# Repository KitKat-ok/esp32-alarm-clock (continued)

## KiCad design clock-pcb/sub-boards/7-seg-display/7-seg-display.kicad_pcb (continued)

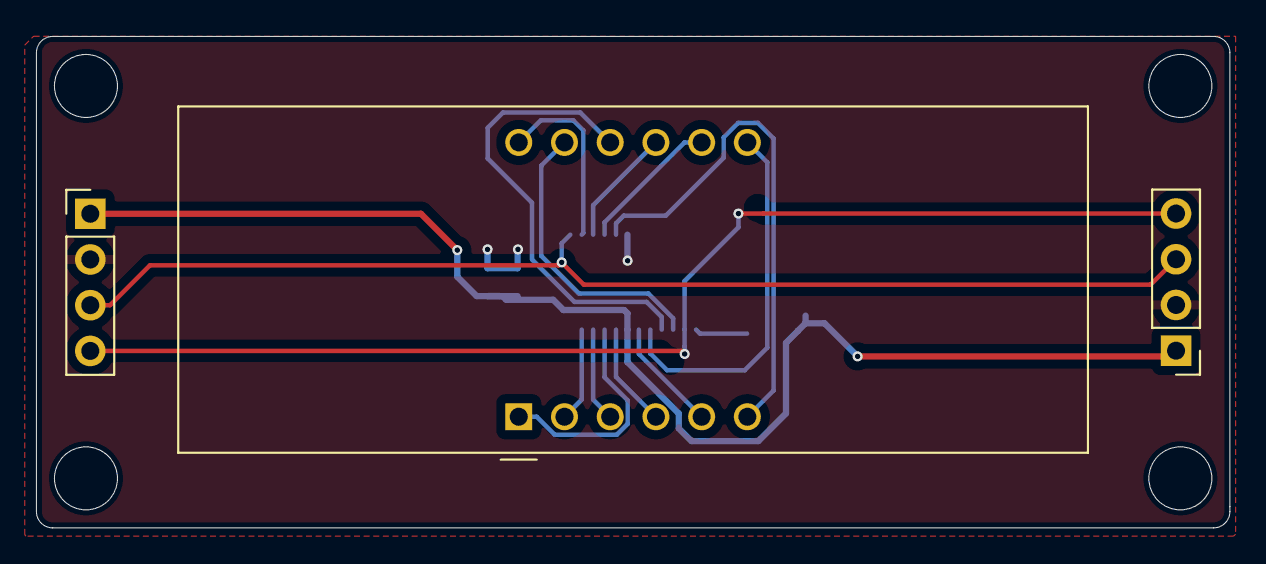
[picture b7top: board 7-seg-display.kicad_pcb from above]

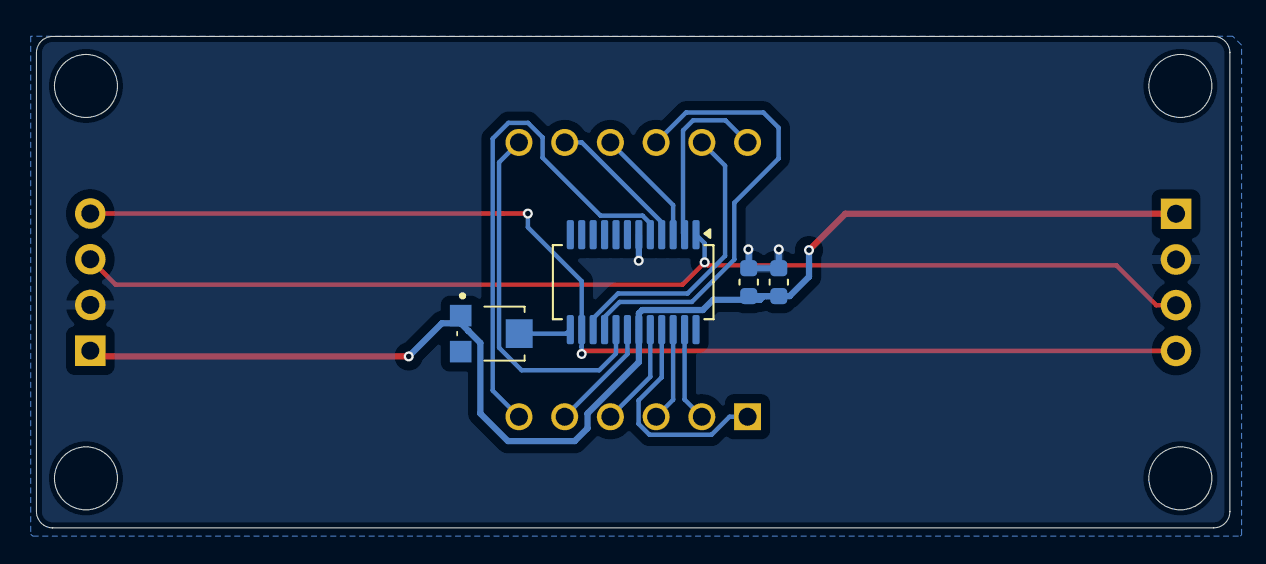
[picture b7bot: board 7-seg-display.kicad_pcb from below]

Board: 2 copper layers, 66.3 x 27.3 mm, 7 parts (4 on the bottom side), 17 nets.

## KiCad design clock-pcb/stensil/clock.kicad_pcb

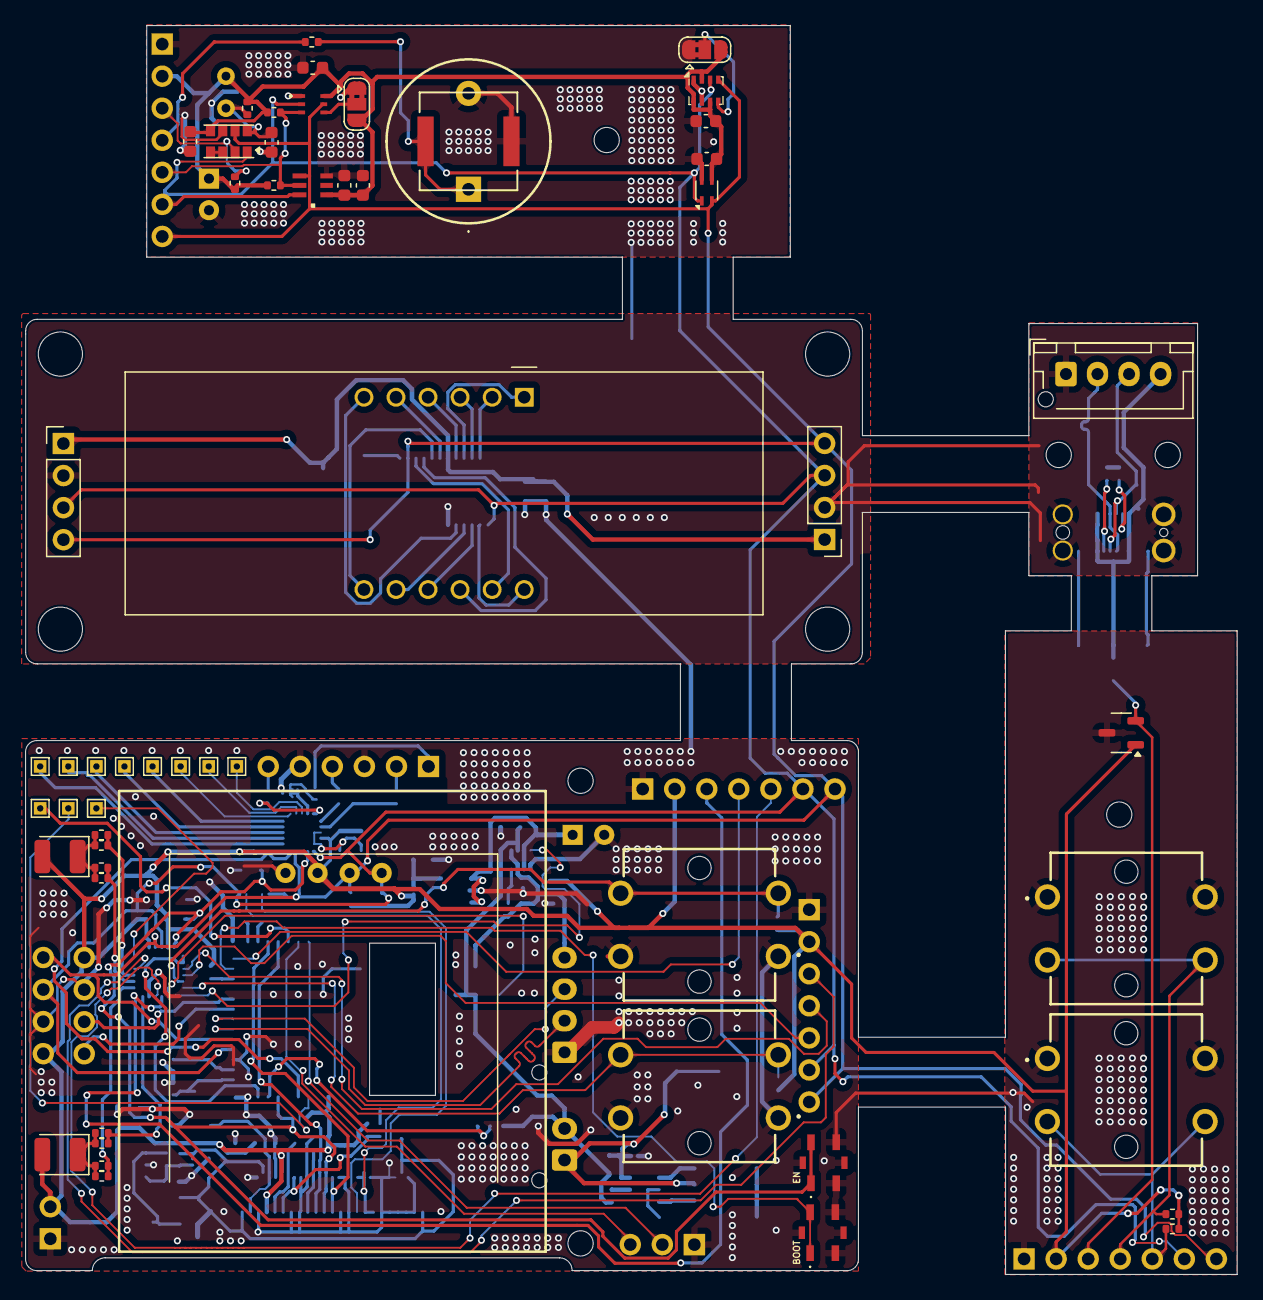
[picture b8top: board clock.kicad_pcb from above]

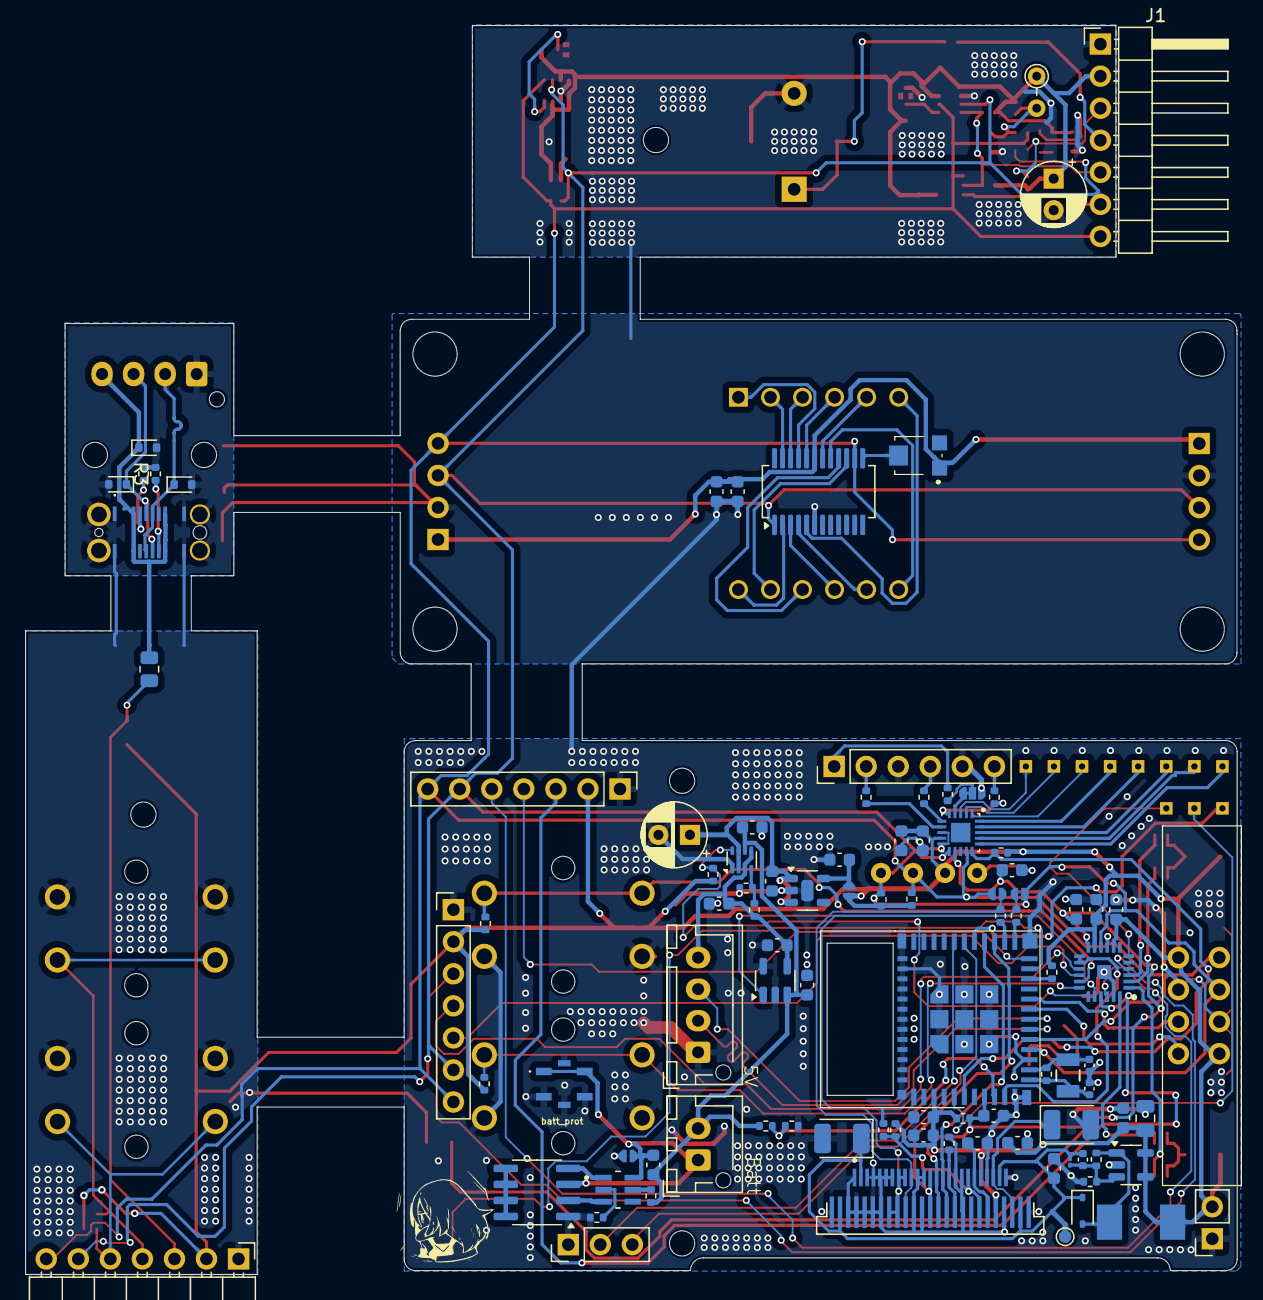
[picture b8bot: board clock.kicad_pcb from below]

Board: 2 copper layers, 96.0 x 99.0 mm, 154 parts (95 on the bottom side), 98 nets.

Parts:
AO9926C1: SOIC-8_3.9x4.9mm_P1.27mm
C1, C1#2, C2, C2#2, C3, C4#2, C6, C23, C23#2: 0.1uF; C_0603_1608Metric
C3#2, C17, C24, C24#2: 10uF; C_0603_1608Metric
C4: 4.7uF; C_0603_1608Metric
C5, C6#2, C7, C8, C9, C10, C11, C12, C13, C13#2, C14, C15, C21, C25, C28: 1uF; C_0603_1608Metric
C5#2, C7#2: 100uF; CP_Radial_D5.0mm_P2.50mm
C16: 4.7uF; C_0805_2012Metric
C18: 6.4pF; C_0402_1005Metric
C19, C20: 19pF; C_0402_1005Metric
C22: 6.4pF; C_01005_0402Metric
C26, C27: 4.7uF; CP_EIA-3528-12_Kemet-T
D1, D2: LED; LED_1210_3225Metric
D1#2, D2#2, D3#2: ESD5Zxx; D_SOD-523
D3: NSVR0340HT1G; D_SOD-323
IC1: VEML6030-GS15; VEML6030GS15
IC2: MCP23018-E_MJ; QFN50P400X400X90-25N-D
J1, J2: Conn_01x04_Socket; PinHeader_1x04_P2.54mm_Vertical
J1#2, J1#3: Conn_01x07_Socket; PinHeader_1x07_P2.54mm_Horizontal
J1#4: Conn_01x03_Pin; PinHeader_1x03_P2.54mm_Vertical
J1#5: USB4145-03-0070-C; USB4145030070C
J2#2: oled 2; SSD1306_0.96_Oled
J3: Led display; tm1637_module
J4: Led display 2; PinHeader_1x04_P2.54mm_Vertical
J5, J6: Conn_01x07_Socket; PinHeader_1x07_P2.54mm_Vertical
J7: SFV25R-2STE1HLF; OLED_1.5IN_128X128MONO
J8, J9: Conn_01x04_Socket; JST_XH_B4B-XH-AM_1x04_P2.50mm_Vertical
J8#2: SFV25R-2STE1HLF; AMPHENOL_SFV25R-2STE1HLF
J11: Conn_01x06_Socket; PinHeader_1x06_P2.54mm_Vertical
J15: Conn_01x02_Socket; PinSocket_1x02_P2.54mm_Vertical
JP1, JP2: SolderJumper_3_Bridged12; SolderJumper-3_P1.3mm_Bridged2Bar12_RoundedPad1.0x1.5mm
JP1#2, JP5, JP6, JP7: Jumper; jumper_solder_small
JP2#2: SolderJumper_3_Bridged12; jumper_solder_small_3_bridged
L1: CPT-14146-80T; CPT1414680T
L1#2: 10uH 1A; HPI0530-100
LS1: Speaker_Crystal; AST0760_MAL
R0, R1#4, R3#2: 5.1k; R_0402_1005Metric
R1, R1#2, R2, R3, R6, R8, R9, R10, R11, R11#2, R15, R16, R28, R30, R31: 10K; R_0402_1005Metric
R1#3, R12, R14: 100k; R_0402_1005Metric
R2#2, R26: 300k; R_0402_1005Metric
R3#3: 800k; R_0402_1005Metric
R4, R4#2: 330R; R_0402_1005Metric
R5: 22R; R_0402_1005Metric
R5#2: 2.7K; R_0402_1005Metric
R6#2: 22R; R_Axial_DIN0204_L3.6mm_D1.6mm_P2.54mm_Vertical
R7: 47K; R_0402_1005Metric
R13: 250k; R_0402_1005Metric
R17, R18, R19, R20, R22, R23, R24, R25: 330; R_0402_1005Metric
R21: 10M; R_0402_1005Metric
R27: 3.16M; R_0402_1005Metric
R29: 1.2M; R_0402_1005Metric
R32, R33: N/A; R_0402_1005Metric
S1, S2, S3, S4: B3F-5050; B3F-4055
S1#2, S2#2, S5: TS21-34-035-BK-160-SMT-TR; TS2134035BK160SMTTR
TP1, TP3, TP4, TP5, TP6, TP7, TP8, TP9, TP10, TP12, TP13: TestPoint; TestPoint_THTPad_1.0x1.0mm_Drill0.5mm
TP2: TestPoint; TestPoint_Pad_D1.0mm
U1: BMP280; Bosch_LGA-8_2x2.5mm_P0.65mm_ClockwisePinNumbering
U1#2: CC56-12EWA; CA56-12EWA
U1#3: TMAG5231C1GQDBZR; SOT-23-3
U1#4: ESP32-C6-MINI-1-N4; XCVR_ESP32-C6-MINI-1-N4
U2: LTR-F216A
U2#2: AS1115-BSST; QSOP-24_3.9x8.7mm_P0.635mm
U2#3: SOT95P280X140-6N
U3: APDS-9960; Avago_APDS-9960
U3#2: JST_XH_B2B-XH-AM_1x02_P2.50mm_Vertical
U4: SHT4x; Sensirion_DFN-4_1.5x1.5mm_P0.8mm_SHT4x_NoCentralPad
U4#2: TPS2116DRL; SOT-583-8
U5: MCP73811T-420I-OT; SOT-23-5
U6: TPS61040DBV; SOT-23-5
U7: TLV75533PDBV; TLV75733PDYDR
U8: AT42QT2120-MMHR; QFN45P300X300X85-21N
VR1: TC33X-2-303E; TC33X2304E
Y2: 32.768KHz; XTAL_9HT10_TXC

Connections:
14V_OLED: C17.1, C18.1, C22.1, C27.1, D3.1 (K), J7.2, J7.24, J8#2.2, J8#2.24, TP2.1
+3.3V: C23.1, C24#2.1, J1.1, J2.1, U2#2.19 (VDD), VR1.1 (CCW)
+3V3: C1.2, C1#2.2, C2.2, C2#2.1, C3.1, C3#2.1, C4.1, C6.2, C7#2.1, C13.1, C15.2, C16.1, C21.2, C23#2.1, C24.1, C28.2, D1.2 (A), D2.2 (A), IC1.6 (VDD), IC2.8 (VDD), IC2.11 (ADDR), J1#2.2, J1#3.2, J2#2.2, J3.4, J4.4, J5.2, J6.2, J7.5, J8#2.21, J15.2, JP1.3 (B), JP2.3 (B), JP7.2 (B), L1#2.2, R0.1, R1.2, R1#2.1, R1#3.1, R2.1, R3.1, R5.1, R6.2, R6#2.1, R7.1, R11.2, R11#2.1, R12.1, R15.2, R28.2, R31.1, U1.2 (CSB), U1.6 (VDDIO), U1.8 (VDD), U1#3.1 (VCC), U1#4.3 (3V3), U2.1 (VDD), U3.5 (LED_A), U4.3 (VDD), U6.4 (EN), U6.5 (VIN), U8.9 (VDD)
+BATT: C4#2.2, C7.1, C11.1, R2#2.1, R4#2.2, U3#2.2, U4#2.6 (VIN2), U5.3 (V_{BAT})
-BATT: AO9926C1.3 (S1), C4#2.1, JP1#2.1 (A), S5.1 (COM_1), S5.2 (COM_2), U2#3.6 (VSS), U3#2.1
ADC: R2#2.2, R3#3.1, U1#4.9 (IO4)
BUTON_CONF: IC2.16 (GPA1), J1#3.5, J6.5, R11.1, S1.3 (NO_1), S1.4 (NO_2)
BUTTON_DOWN: IC2.18 (GPA3), R28.1, S4.3 (NO_1), S4.4 (NO_2)
BUTTON_EXIT: IC2.15 (GPA0), J1#3.4, J6.4, R1.1, S2.3 (NO_1), S2.4 (NO_2)
BUTTON_UP: IC2.17 (GPA2), R15.1, S3.3 (NO_1), S3.4 (NO_2)
BUZZER: J1#2.4, J5.4, R4.2, U1#4.24 (IO18)
BUZZER_IN: L1.1, LS1.1, R4.1
CHARGE_EN: IC2.20 (GPA5), U5.1 (CE)
CLK: J4.1, U1#4.19 (IO14)
CLOCK_N: C19.1, R21.1, U1#4.13 (IO1), Y2.1
CLOCK_P: C20.1, R21.2, U1#4.12 (IO0), Y2.2
CS: J7.11, J8#2.15, U1#4.28 (IO22)
DC: J7.13, J8#2.13, U1#4.27 (IO21)
DIGIT-1: U1#2.12 (CC1), U2#2.2 (DIG0)
DIGIT-2: U1#2.9 (CC2), U2#2.3 (DIG1)
DIGIT-3: U1#2.8 (CC3), U2#2.4 (DIG2)
DIGIT-4: U1#2.6 (CC4), U2#2.5 (DIG3)
DIO: J4.2, U1#4.20 (IO15)
DN: D2#2.1 (K), J1#5.A7 (DN1), J1#5.B7 (DN2), J8.2, J9.2, U1#4.17 (IO12)
DP: D3#2.1 (K), J1#5.A6 (DP1), J1#5.B6 (DP2), J8.3, J9.3, U1#4.18 (IO13)
EN: C12.2, C13#2.1, C14.2, IC2.12 (~RESET), J7.12, J8#2.14, R11#2.2, S2#2.1 (COM_1), S2#2.2 (COM_2), U1#4.8 (EN), U8.12 (~RESET)
GND: AO9926C1.1 (S2), C1.1, C1#2.1, C2.1, C2#2.2, C3.2, C3#2.2, C4.2, C5.2, C5#2.2, C6.1, C6#2.1, C7.2, C7#2.2, C8.2, C9.2, C10.2, C11.2, C12.1, C13.2, C13#2.2, C14.1, C15.1, C16.2, C17.2, C19.2, C20.2, C21.1, C23.2, C23#2.2, C24.2, C24#2.2, C25.1, C26.2, C27.2, C28.1, D1#2.2 (A), D2#2.2 (A), D3#2.2 (A), IC1.1 (GND), IC2.23 (VSS), IC2.25 (EP), J1.2, J1#2.1, J1#3.1, J1#4.1, J1#5.A1 (GND_1), J1#5.A12 (GND_2), J1#5.B1 (GND_3), J1#5.B12 (GND_4), J1#5.MH1, J1#5.MH2, J1#5.MH3, J1#5.MH4, J2.2, J2#2.1, J3.3, J4.3, J5.1, J6.1, J7.1, J7.4, J7.8, J7.9, J7.14, J7.15, J7.19, J7.20, J7.21, J7.22, J7.23, J7.25, J8.1, J8#2.1, J8#2.3, J8#2.4, J8#2.5, J8#2.6, J8#2.7, J8#2.11, J8#2.12, J8#2.17, J8#2.18, J8#2.22, J8#2.25, J9.1, J11.3, J11.5, J15.1, JP1.1 (A), JP1#2.2 (B), JP2.1 (A), JP2#2.3 (B), L1.2, LS1.2, R1#4.2, R3#2.2, R3#3.2, R5#2.2, R14.1, R26.2, R29.2, R30.1, S1.1 (COM_1), S1.2 (COM_2), S1#2.3 (NO_1), S1#2.4 (NO_2), S1#2.MP1, S1#2.MP2, S2.1 (COM_1), S2.2 (COM_2), S2#2.3 (NO_1), S2#2.4 (NO_2), S2#2.MP1, S2#2.MP2, S3.1 (COM_1), S3.2 (COM_2), S4.1 (COM_1), S4.2 (COM_2), S5.3 (NO_1), S5.4 (NO_2), S5.MP1, S5.MP2, U1.1 (GND), U1.7 (GND), U1#3.3 (GND), U1#4.1 (GND1), U1#4.2 (GND1__1), U1#4.11 (GND1__2), U1#4.14 (GND1__3), U1#4.36 (GND1__4), U1#4.37 (GND1__5), U1#4.38 (GND1__6), U1#4.39 (GND1__7), U1#4.40 (GND1__8), U1#4.41 (GND1__9), U1#4.42 (GND1__10), U1#4.43 (GND1__11), U1#4.44 (GND1__12), U1#4.45 (GND1__13), U1#4.46 (GND1__14), U1#4.47 (GND2), U1#4.48 (GND2__1), U1#4.49_1 (GND2__2), U1#4.49_2 (GND2__3), U1#4.49_3 (GND2__4), U1#4.49_4 (GND2__5), U1#4.49_5 (GND2__6), U1#4.49_6 (GND2__7), U1#4.49_7 (GND2__8), U1#4.49_8 (GND2__9), U1#4.49_9 (GND2__10), U1#4.50 (GND2__11), U1#4.51 (GND2__12), U1#4.52 (GND2__13), U1#4.53 (GND2__14), U2.3 (GND), U2#2.6 (GND), U3.6 (GND), U4.4 (VSS), U4#2.1 (GND), U5.2 (V_{SS}), U5.5 (PROG), U6.2 (GND), U7.2 (GND), U8.8 (VSS), U8.10 (MODE)
GPIO9: S1#2.1 (COM_1), S1#2.2 (COM_2), U1#4.23 (IO9)
GUARD: JP2#2.1 (A), JP2#2.2 (C), R9.2, U8.4 (KEY3/GPO1)
HALL_SENS: IC2.4 (GPB4), J1#3.3, J6.3, U1#3.2 (OUT)
INT_A: IC2.13 (INTB), IC2.14 (INTA), U1#4.10 (IO5)
LDO_IN: C5#2.1, C9.1, U4#2.2 (VOUT), U4#2.7 (VOUT), U7.1 (IN), U7.3 (EN)
LED1_P1: IC2.24 (GPB0), R17.1, R19.1
LED1_P2: IC2.1 (GPB1), R18.1, R20.1
LED2_P1: IC2.2 (GPB2), R22.1, R23.1
LED2_P2: IC2.3 (GPB3), R24.1, R25.1
MOSI: J7.17, J7.18, J8#2.8, J8#2.9, JP5.2 (B), R33.1
unnamed: AO9926C1.5 (D1), AO9926C1.6 (D1), AO9926C1.7 (D2), AO9926C1.8 (D2)
unnamed: AO9926C1.4 (G1), U2#3.1 (DO)
unnamed: AO9926C1.2 (G2), U2#3.3 (CO)
unnamed: C25.2, J7.6, J8#2.20
unnamed: C26.1, J7.3, J8#2.23
unnamed: D1.1 (K), R17.2, R18.2, R19.2, R20.2
unnamed: D2.1 (K), R22.2, R23.2, R24.2, R25.2
unnamed: D3.2 (A), L1#2.1, R27.1, U6.1 (SW)
unnamed: IC1.4 (ADDR), JP1.2 (C)
unnamed: IC2.6 (GPB6), TP10.1
unnamed: J1#5.A5 (CC1), R1#4.1
unnamed: J1#5.B5 (CC2), R3#2.1
unnamed: J7.7, J8#2.19, R30.2, R31.2
unnamed: J7.10, J8#2.16, R29.1
unnamed: J11.1, R9.1
unnamed: J11.2, R16.1
unnamed: J11.4, R10.1
unnamed: J11.6, R8.1
unnamed: JP2.2 (C), U1.5 (SDO)
unnamed: C8.1, JP7.1 (A), U7.5 (OUT)
unnamed: U1#2.3 (DPX), U2#2.22 (SEGDP)
unnamed: TP9.1, U1#4.5 (IO2)
unnamed: R0.2, U1#4.22 (IO8)
unnamed: R33.2, U1#4.25 (IO19)
unnamed: R32.2, U1#4.26 (IO20)
unnamed: TP1.1, U1#4.29 (IO23)
unnamed: U1#2.11 (a), U2#2.15 (SEGA)
unnamed: U1#2.7 (b), U2#2.17 (SEGB)
unnamed: U1#2.4 (c), U2#2.20 (SEGC)
unnamed: U1#2.2 (d), U2#2.23 (SEGD)
unnamed: U1#2.1 (e), U2#2.21 (SEGE)
unnamed: U1#2.10 (f), U2#2.16 (SEGF)
unnamed: U1#2.5 (g), U2#2.18 (SEGG)
unnamed: U2#2.13 (ISET), VR1.2 (WIPER)
unnamed: R4#2.1, U2#3.5 (VDD)
unnamed: R5#2.1, U2#3.2 (VM)
unnamed: U3.3 (LDR), U3.4 (LED_K)
unnamed: C5.1, R5.2, R6#2.2, U3.8 (VDD)
unnamed: R13.1, R14.2, U4#2.4 (PR1)
unnamed: C18.2, C22.2, R26.1, R27.2, U6.3 (FB)
unnamed: TP13.1, U8.3 (KEY4/GPO2)
unnamed: TP12.1, U8.2 (KEY5/GPO3)
unnamed: TP8.1, U8.1 (KEY6/GPO4)
unnamed: TP7.1, U8.20 (KEY7/GPO5)
unnamed: TP6.1, U8.19 (KEY8/GPO6)
unnamed: TP5.1, U8.18 (KEY9/GPO7)
unnamed: TP4.1, U8.17 (KEY10/GPO8)
unnamed: TP3.1, U8.16 (KEY11/GPO9)
POWER_STATUS: IC2.19 (GPA4), R6.1, U4#2.8 (ST)
RX: J1#4.3, U1#4.30 (RXD0)
SCL: IC1.5 (SCL), IC2.9 (SCL), J1.4, J1#2.7, J1#3.7, J2.4, J2#2.3, J3.1, J5.7, J6.7, JP6.1 (A), R1#3.2, U1.4 (SCK), U1#4.16 (IO7), U2.4 (SCL), U2#2.14 (SCL), U3.7 (SCL), U4.2 (SCL), U8.14 (SCL)
SCLK: J7.16, J8#2.10, JP6.2 (B), R32.1
SDA: IC1.2 (SDA), IC2.10 (SDA), J1.3, J1#2.6, J1#3.6, J2.3, J2#2.4, J3.2, J5.6, J6.6, JP5.1 (A), R12.2, U1.3 (SDI), U1#4.15 (IO6), U2.6 (SDA), U2#2.1 (SDA), U3.1 (SDA), U4.1 (SDA), U8.11 (SDA)
SLID_0: R16.2, U8.7 (KEY0)
SLID_1: R10.2, U8.6 (KEY1)
SLID_2: R8.2, U8.5 (KEY2/GPO0)
SUB_TOP_1: IC1.3 (INT), IC2.22 (GPA7), J1#2.5, J5.5, R1#2.2, R2.2, U2.5 (INT)
SUB_TOP_3: IC2.21 (GPA6), J1#2.3, J5.3, R3.2, U3.2 (INT)
TOUCH_INT: R7.2, U1#4.6 (IO3), U8.15 (~CHANGE)
TX: J1#4.2, U1#4.31 (TXD0)
VBUS: C6#2.2, C10.1, D1#2.1 (K), J1#5.A4 (VBUS_1), J1#5.A9 (VBUS_2), J1#5.B4 (VBUS_3), J1#5.B9 (VBUS_4), J8.4, J9.4, R13.2, U4#2.3 (VIN1), U4#2.5 (MODE), U5.4 (V_{DD})

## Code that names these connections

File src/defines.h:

#ifndef DEFINES_H
#define DEFINES_H

#include "fonts/fonts.h"
#include "weather/weathericons.h"

#include <Arduino.h>
#include <Adafruit_GFX.h>
#include <Adafruit_SSD1306.h>
#include <TM1637Display.h>
#include <BH1750.h>
#include <WiFi.h>
#include <WiFiMulti.h>
#include <TimeLib.h>
#include <NTPClient.h>
#include <Preferences.h>
#include <OneWire.h>
#include <DallasTemperature.h>
#include <oledManager.h>

extern bool OTAEnabled;

// Led Display
#define CLK  19 // The ESP32 pin GPIO22 connected to CLK
#define DIO  18 // The ESP32 pin GPIO23 connected to DIO

// NTP
#define TIME_OFFSET_S 3600            // Time offset in seconds, use this as timezones

// Weather
#define DAILY_WEATHER_INTERVAL 5 * 60 * 60 * 1000
#define CURRENT_WEATHER_INTERVAL 30 * 60 * 1000  // 30 minutes

// Light Sensor
#define OLED_DISABLE_THRESHOLD 45
#define LED_DIM_THRESHOLD 30
#define LED_DISABLE_THRESHOLD 1

#define MAX_INCREASE_OF_LIGHT_LEVEL 1000

// Inputs
#define BUTTON_UP_PIN      GPIO_NUM_12
#define BUTTON_DOWN_PIN    GPIO_NUM_13
#define BUTTON_CONFIRM_PIN GPIO_NUM_14
#define BUTTON_EXIT_PIN    GPIO_NUM_15

#define MAX_MENU_ITEMS 15
#define MAX_ALARMS 15


#define TOUCH_BUTTON_PIN 4
#define TOUCH_BUTTON_THRESHOLD 8
#define TOUCH_BUTTON_THRESHOLD_WHEN_ALREADY_TOUCHED 8
#define TOUCH_BUTTON_THRESHOLD_ON_BATTERY 9

#define NUM_TOUCH_SAMPLES 10

// Menus
#define TOTAL_NAV_BUTTONS 4
#define MAX_DEPTH 20

#define MAIN_PAGE_DURATION 60000
#define SCREENSAVER_DURATION 30000

#define N_FLYERS 5  // Numver of flyers on screensaver

#define fontX 6
//5
#define fontY 12

// Alarm
#define SUNDAY    0
#define MONDAY    1
#define TUESDAY   2
#define WEDNESDAY 3
#define THURSDAY  4
#define FRIDAY    5
#define SATURDAY  6

// Buzzer
#define BUZZER_PIN 27
//#define START_SOUND false // uncomment to enable start sound

// Battery
#define MIN_VOLTAGE 3.40  // Minimum voltage of LiPo battery
#define MAX_VOLTAGE 4.20  // Maximum voltage of LiPo battery
#define NUM_SAMPLES 15   // How many samples to read to smooth the voltage out

#define VOLTAGE_DIVIDER_PIN 34 

#define FULLY_CHARGED_PIN 32
#define CHARGING_PIN 33

#define TIMER_WAKUP_TIME 15000 // In miliseconds
#define GPIO_WAKUP_TIME 30000 // In miliseconds
#define SLEEPING_TIME 60 * 1000000 

#define CHARGING_THRESHOLD 1000
#define STANDBY_THRESHOLD 1000

// Temperature
#define TEMP_SENS_PIN 5
#define TEMP_CHART_READINGS 55 // Number of readings to keep

#define TEMP_OFFSET 2.77


#include "hardware/pitches.h"

#include "confidential.h"

#include "hardware/hardware.h"
#include "functions.h"
#include "WiFi/WiFi.h"
#include "NTP/NTP.h"
#include "weather/weather.h"
#include "LedDisplay/LedDisplay.h"
#include "lightSensor/lightSensor.h"
#include "oledDisplay/interface.h"
#include "oledDisplay/mainPage.h"
#include "oledDisplay/charts.h"
#include "oledDisplay/menus.h"
#include "Flash/Flash.h"
#include "alarms/alarms.h"
#include "battery/battery.h"
#include "tempSensor/tempSensor.h"


#endif

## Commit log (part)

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2023-12-31 platformio
2024-01-01 touch button
2024-01-04 battery
2024-01-05 battery not working
2024-01-09 sleep management
2024-01-10 temperature
2024-01-11 Temp chart
2024-01-12 temp working yep maybe
2024-01-13 temp sync
2024-01-13 fixed the chart
2024-01-16 weather menu menu fixes and light chart
2024-01-16 to do
2024-01-21 different temp sensor
2024-02-04 test?
2024-03-20 probably fixed a few bugs
2024-04-04 fixed many issues
2024-04-13 fixes of crashes, added debug menus
2024-04-19 added ringing bool and fixed the brightness modulation
2024-04-21 forgot to save the soundOn variable....
2024-04-23 completly redesigned the main page
2024-04-26 cleaned up files
2024-04-26 added comment
2024-05-01 probably fixed some issues with light readings
2024-05-03 fixed a bit of weather menus
2024-05-07 fixed name of alarm structure and added confidential file
2024-05-07 chaged gitignore
2024-05-07 test
2024-05-07 test2
2024-05-07 added confidential
2024-05-07 cleaned up
2024-05-08 cleaned up code again...
2024-05-08 cleaned up again
2024-05-09 checking for night is now dependant on alarms
2024-05-10 cleaned up some stuff
2024-05-11 changed ringing alarm structure
2024-05-11 didnt compile lol
2024-05-11 fixed wrong if
2024-05-23 fixed file name and added OTA in menus
2024-05-25 time wasnt updating on alarm
2024-06-06 fixed a bit of stuff
2024-06-16 added screensaver to prevent burnin
2024-06-17 added second main to sleep menu and dimming is better
2024-06-21 fixed bugs
2024-06-22 fixed crashes and started using internal rtc to keep time even if a crash occurs
2024-06-22 added voltage to debug changed start sound
2024-06-23 fixed alighnment on main menu
2024-06-27 changed threshold
2024-07-01 changed some stuff
2024-07-25 cleaned up code, switched to openmeteo, fixed bugs
2024-07-25 changed confidential file
2024-07-25 updated plaformio.ini
2024-07-25 added a delay
2024-07-25 moved link to confidential
2024-07-25 changed somethins
2024-07-27 coment
2024-08-03 new icons a lot of fixes and new menus
2024-08-03 todo make proper displaying manager
2024-08-04 lowered i2c speed and gave up on manager
2024-08-04 added oled listener
2024-08-06 made working oled manager.... gjifdosjgiopdj
2024-08-07 works
2024-08-07 fixed display enabling disabling
2024-08-11 fixed a few stuff
2024-08-11 fixed maybe
2024-08-12 changed vallue
2024-08-15 fixed reading light
2024-09-18 new menu not complete
2024-09-18 added idle to menu system
2024-09-19 now max menu size of submenus can be set independetly of the MAX_MENU_SIZE
2024-09-21 cleaned unnecesary libs
2024-09-30 git broke?
2024-10-01 half working alarm menu?
2024-10-02 still not working properly
2024-10-18 half ability to set day...
2024-11-11 the pcb
2024-12-19 light sens batt sens
2024-12-21 temp sens and interface fix?
2024-12-24 charger management
2024-12-26 alarm menu init works
2024-12-27 alarm management draft
2024-12-27 manage alarms and sht40 main page
2024-12-28 fix delete alarms and name adjustment
2024-12-29 weather menus
2024-12-29 charts
2024-12-30 hysterisi to screen management
2024-12-30 fixed sleep
2024-12-30 fixed display brightness management
2024-12-31 fiixed menu scrolling on battery
2025-01-01 esp idf
2025-01-01 fixed wifi
2025-01-01 better clock source
2025-01-05 menus and battery fixes
2025-01-07 werent saving day of alarms
2025-01-10 fixed alarms werent working before aaaaa
2025-01-12 fix alarm menu and add support for hall switch
2025-01-14 fix alarm not ringing and menu fix
2025-01-18 integration for milight
2025-01-18 fix warning
2025-01-18 clean up files and gitignore
2025-01-18 remove more unnecessery files
2025-01-18 gitignore
2025-01-18 clean
2025-01-19 some fixes
2025-01-24 button manager draft
2025-01-24 button manager working
2025-01-25 fix random bugs
2025-01-25 show n/a when no weather
2025-01-25 flickering screen "fixed"
2025-01-25 add back delay...
2025-01-26 fix stupid bugs
2025-01-27 fix for when no responce from milight
2025-01-27 aaaa
2025-01-27 stop spamming requests...
2025-07-26 remove unused variables and update to newest idf version
2025-07-26 increase stack size
2025-07-29 increase stack size alarms
2025-08-07 new pcb
2025-08-08 routing
2025-08-27 touch slider pcb
2025-08-30 voltage regulator
2025-09-14 panel
2025-11-01 not compiling yet
2025-11-02 compiles
2025-11-02 compiles button no work
2025-11-08 buttons work..
2025-11-10 touch draft
2026-01-06 touch detected
2026-04-22 new pcb drafts
2026-04-22 pragma once and pressure sensor
2026-04-23 touch fixes smooth led brightness
2026-04-25 touch reading and other improvements
2026-04-26 icons
2026-04-27 proper icon generation
2026-05-10 proper display settings and others
